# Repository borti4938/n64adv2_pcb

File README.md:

N64 Advanced 2 (PCB)
---

This repository contains all you need files to build your own DIY N64 Advanced board.
Firmware is supplied in another repository.

Please don't ask me for selling a modding.
I either sell some prototypes on some forums marketplaces (which is very unlikely) or I don't have any of the boards.
This is a complete DIY modding project.
Everybody is on his own here.

**WARNING:**
This is an advanced DIY project if you do everything on your own.
You need decent soldering skills.
The FPGA ad Video transmitter have 0.5mm fine pitch with 144pins and 64pins, respectively, and each has an exposed pad below the IC, which has to be soldered to the PCB.
Furthermore, the clocking chip is in a 24-QFN package where the pins are partwise below the IC.
It also has an exposed pad.
Next to it on the board there are some SMD1206 resistor and ferrite bead arrays.

One note on KiCad: please do not use version 7 and stay with version 6.xx.yy, if you want to edit the PCB.
I have to adapt the design files first before there are working as intended in version 7.
Thanks!

## Table of Contents

- [Checklist](https://github.com/borti4938/n64adv2_pcb#checklist-how-to-build-the-project)
- [Assembly](https://github.com/borti4938/n64adv2_pcb#assembly)
- [PCB Specs](https://github.com/borti4938/n64adv2_pcb#pcb-specs)
- [Installation](https://github.com/borti4938/n64adv2_pcb#installation)
  - [1. Open the Console](https://github.com/borti4938/n64adv2_pcb#1-open-the-console)
  - [2. Preparation](https://github.com/borti4938/n64adv2_pcb#2-preparation)
  - [3. Solder Work](https://github.com/borti4938/n64adv2_pcb#3-solder-work)
  - [4. Testing Installtion](https://github.com/borti4938/n64adv2_pcb#4-testing-installation)
  - [5. Put Everything Together](https://github.com/borti4938/n64adv2_pcb#5-put-everything-together)
- [Installation with UltraPIF](https://github.com/borti4938/n64adv2_pcb#installation-with-ultrapif)
- [Jumper Description](https://github.com/borti4938/n64adv2_pcb#jumper-description)

## Checklist: How to build the project

- Use PCB files to order your PCBs. You need the order the main PCB. If you plan to have a clean install, you need to order a flexible PCB, too. You can opt for a fully custom flex-PCB or a partial flex-PCB where you run a FFC cable from flex to main PCB. Important PCB specifications are provided in the [BOM](./doc/n64adv2_BOM.xlsx).
  - Main PCB: either [KiCAD-PCB design file](./pcbs/main/n64adv2.kicad_pcb) or [Gerber files](./gerber/main/)
  - Full Flex PCB: either [KiCAD-PCB design file](./pcbs/flex/rcp2n64adv2.kicad_pcb) or [Gerber files](./gerber/full_flex/)
  - Partial Flex PCB: either [EAGLE-PCB design file](./pcbs/flex/rcp2fpc_v5.brd) or [Gerber files](./gerber/part_flex/)
- If you plan to use solder paste, do not forget to order a stencil for top and bottom, too
- Source the components you need, e.g. from Mouser or Digikey.
  The BOM is available in [here](./doc/n64adv2_BOM.xlsx).
- If you want to use a assembly service (PCBA), you have to generate position files and BOM (in format as the fab requests it) out of the PCB design files. For JLCPCB e.g., there is a [KiCad plugin](https://github.com/Bouni/kicad-jlcpcb-tools) available (which I yet didn't test).
- Wait for everything to arrive
- Assemble your PCB if you haven't use a PCBA service
- Flash the firmware ([firmware releases](https://github.com/borti4938/n64adv2_fw/releases)) after installing:
  - Use the POF programming file named n64adv2\__fpga-device_.pof
  - Using the intelFPGA programmer, JTAG chain is initialized by loading POF file
  - Select CFM0 and UFM for program and verify
  - N64 needs to be powered for flashing
  - Power cycle the N64 after flashing

## PCB Specs

- **Main-PCB** Use PCB files (either [KiCAD-PCB design file](./pcbs/main/n64adv2.kicad_pcb) or [Gerber files](./gerber/main/)) to order your own PCB with following specs (might be not comprehensive)  
  - Size: 89.6mm x 80.0mm
  - Layer: 4
  - FPC thickness: 1.6mm
  - Min hole size: dia 0.3mm / ring 0.6mm or lower
  - Min trace width / spacing: 0.2mm
- **Flex-PCB** Use PCB files (either [KiCAD-PCB design file](./pcbs/flex/rcp2n64adv2.kicad_pcb) or [Gerber files](./gerber/full_flex/)) to order your own PCB with following specs (might be not comprehensive)  
  - Size: 129.6mm x 25.0mm
  - Layer: 2
  - FPC thickness: 0.15mm \[1\]
  - Min hole size: dia 0.25mm / ring 0.45mm or lower
  - Min trace width / spacing: 0.2mm
  - Stiffener: PI top + bottom
  - Stiffener thickness: 0.15mm \[1\]

\[1\] You may have to vary FPC thickness and stiffener thickness depending on the prototype service you are going with. E.g., on my last order I opted for 0.12mm PCB thickness and 0.225mm polyimide thickness.

## Assembly

If you have all components available, you can start assembly your board.
You can use the [interactive BOM](./doc/n64adv2_main_ibom.html), which helps you organizing your work.
It is just a matter of time and effort to assembly everything.

Note that the FPGA has an exposed pad, which needs a good connection.
Otherwise, the FPGA will not boot at all.
Preheat the FPGA with a hot air gun and solder the exposed pad from bottom if you do not use solder paste.
If you only have your solder iron, apply heat from bottom.
You must be patient at this point as there are large GND planes around the FPGA.
You may check the FPGA temperature with your finger on the top side (once it gets too hot to touch, you may stop for soldering for a moment).
Do the same with the other chips which have an exposed pad (U2 and U4).

If you populate X2 with the THT variant, which is the JTAG connector, please short the pins such that they are flush at the bottom side.
Otherwise, the PCB might be lifted in its position which produces unnecessary mechanical stress on PCB and HDMI connector.

Using non-clean flux (rosin based) is obviously recommended.
Even though it is "non-clean" I recommend cleaning everything afterwards (just for the visual finish).

Please double check everything for shorts once you finished your work.
Very important is that the power supply trace do not short to GND.
- 5V against GND (e.g. at input pads)
- 3.3V against GND (e.g. at input pads)
- 2.5V against GND (e.g. at C14)
- 2.5V against GND (e.g. at C15)
- 3.3V against GND (e.g. at C132)
- 1.8V against GND (e.g. at C122)

## Installation

### 1. Open the console

- Remove Jumper Pak / Expansion Pak
- Remove screws from bottom side of the console  
(needs a 4.5mm gamebit tool)
- Lift top housing
- remove inner screws as marked  
(in very last consoles made the heat sink design changed slightly)
- pull out the mainboard
- remove heat sink and RF shield
- **Hint** Now you have the chance to clean up your N64 shell

(image by Zerberus (circuit-board.de user))

### 2. Preparation

It is possible to do a cut or a no-cut installation.
You will need the following parts for it:

1. N64Adv2 PCB
2. Flex Cable
3. Two to four of washers (M3)
4. Thermal pad
  - Cut Mod: appr. 1mm to 1.5mm thickness
  - No Cut Mod: appr. 2.5mm to 3.0mm thickness
5. 3D printed parts:
  - Cut Mod: [USB port round filler](./prints_3d/HalfCut/N64Adv2_USB_RoundFiller.stl), [JTAG spacer](./prints_3d/HalfCut/N64Adv2_JTAG_Spacer.stl) and [MultiOut replacement](./prints_3d/HalfCut/N64Adv2_MultiOut_HalfCut.stl)
  - No Cut Mod: [PCB lift bracket](./prints_3d/NoCut/N64Adv2_PCB_lift.stl) and [MultiOut replacement](./prints_3d/NoCut/N64Adv2_MultiOut_NoCut.stl)

#### 2.1 Shell Preparation Cut Mod

The bottom shell needs a cutout at the MultiOut port.

Mark the place you need to file with either the N64Adv2 PCB or the 3D printed MultiOut replacement.

File down the shell within your markings until the N64Adv2 sits flush on the shell floor.
Consider a tiny space below the HDMI connector.
Cleanup the shell and place the 3D printed parts into the shell.
Make a final fit test as shown.

#### 2.2 Shell Preparation No Cut

There is no need to cut the shell at all with this variant.
All you need is to remove the bottom RF shield from the N64 mainboard.

Place all 3D printed parts and make a fitting test as shown.

### 3. Solder Work

You have the options to either install everything with casual installation wires or using flex cables.
This is just a trade-off between personal installation effort and price.
Personally, I recommend using the flex cable.
Also with the flex cable you have the option to use a fully custom flex or a partial flex which just have a FFC connector on it to run a FFC cable from N64 to N64Adv2.

The instruction shows the installation with the fully custom flex.
The partial flex installation is similar, but not shown here.
The wired installation is not shown and not documented at all! (at least for the moment)

#### 3.1 Prepare the Flex Cable

The flex cable will be routed through the RF shield.
Close to it there are some capacitors.
Gently bend the flex cable between resistors and protection area (stiffener at top and bottom) as shown.
This relaxes routing with as low stress on the flex cable as possible.

If you opt for the partial flex, postpone this step until you have the partial flex installed (after step 3.2).
Measure where the FFC cable needs to be bend.
Apply some insulation tape for cable protection behind the bending area.

#### 3.2 Flex Cable Installation

Place the flex cable to the RCP-NUS output pins 6 to 28 as shown.
Put the solder area on to of the pins.
(However, putting them in front is also possible.)

Secure the cable with some kapton tape or with two solder joints.
Make sure that solder pads and pins are perfectly aligned.
The better the alignment is the easier is the solder work.

Apply solder to all pins.
Double check for shorts and good connections with a continuity tester of a digital multimeter.

Solder 3.3V, 5V, Reset and Controller legs to the N64 as shown.

Short summary:
- Solder the RCP connector side to the RCP-NUS as shown
  - first pin bottom – 6
  - last pin to – 28
- Connect 3.3V to the flex, e.g. taken from C141
- Connect 5V to the flex, e.g. taken from U13
- Connect Ctrl. and reset
  - reset from PIF-NUS pin 27
  - Controller from PIF-NUS pin 16  
  (Make sure that PIF-NUS pin 16 is connected to the middle pin of controller port 1, otherwise search for a suitable connection point)
- If you have a CPLD-based RGB mod, you can use J3 to setup VI-DeBlur on that mod over the N64Adv2
  - J3 has two pads: the left one (directly above the N64Adv2 logo) is the feedback signal, the other one is GND.
    Use a DMM if you are unsure (the GND pad has connection to any GND point on the N64 mainboard if flex is installed)
  - J3 signal pad is high on VI-DeBlur disabled and goes low if enabled

#### 3.2a Flex Cable Version 20231105 (and later)

With Version 20231105 the flex cable was redesigned at the ends to controller and reset connection at the PIF-NUS.

Changes were:
- No components anymore on the thin cable ends for easier handling
- Using a single gate buffer (U1) for the controller line is now mandatory.
- Backup pads for controller and reset connection of the thin cable breaks.
  If cable breaks you can simply cut off the broken cable end and route a separate wire from PIF pin to the backup pad.

#### 4. Testing Installation

At this point it is a good idea to test your installtion.

First you should check for some obvious short at the power rails, e.g. between 3.3V and GND, and between 5V and GND.
If the N64Adv2 board is connected with the flex, you can simply use the input pads on the N64Adv2 board.

Insert a game cartridge, connect HDMI and power, and turn on your N64!
**Important:** If you do not have heatsinks attached to your N64, only test for a brief moment.

Obviously, the firmware of the N64Adv2 must be flashed to the FPGA.

If you see a picture with game output and here some game audio, then everything might be ok.
It's a good idea to run the debug-screen for a quick check.
If something is not ok, the N64Adv2 hardware should boot into the debug screen by default.
Then you have to go for debugging your installation.

Additional information on flashing the firmware and how to debug with the debug screen, can be found the [firmwares repository](https://github.com/borti4938/n64adv2_fw).

#### 5. Put Everything Together

Secure your installation from shorts to the top RF shield with some insulation tape.
There is a risk for shorts where the controller leg of the full flex is routed.
Everything else is safe.

Place some washer (about 0.5mm to 1mm height) at the screw spots left and right of the N64Adv2 flex cable.
From my experience it is easier to secure them with some tape.
Close the RF shield of the N64 then.

Now connect the N64Adv2 PCB to the flex cable.
For the Cut-Mod, also place the bottom RF shield into its place of the N64.
The RF shield does not fit in the no-cut mod variant.

Put the thermal pad on top of the FPGA (U1) of the N64Adv2 board.
This helps with heat dissipation and holds the PCB in its place.

Put everything in the bottom shell.
Do not forget 3D printings.

Secure the N64 with two or three screws and make a small test to see if everything is working.
Do not forget to put in the Jumper Pak or Expansion Pak, otherwise you won't see a picture at all.

If everything works fine, close the whole shell.

## Installation with UltraPIF

This guide assumes that the UltraPIF will be installed after the N64Adv2.
However, other installation orders are possible, too - i.e. UltraPIF first and then N64Adv2 or both alongside.
There are not described, here.
For the ease of debugging, installation one after the other is always recommended.

Also, it is not described, how to open and close the N64.

### 1. Remove PIF-NUS

To remove the PIF-NUS, remove reset and controller connections, first.

The remove the PIF-NUS.

### 2. Install UltraPIF Adapter Board

Put the UltraPIF board into its place.
Connect clock and mode wires and if you want, the RGB led board.
More details on that can be found in the [UltraPIF Repository](https://github.com/jago85/UltraPIF_Hardware/wiki/Installation).

### 3. Connect Flex Cable

Once the UltraPIF Adapter sits in its place, you can reconnect the reset and controller connections of the flex cable.

For the controller connection, you can use the _CON_ pad on the adapter.

For the reset connection you have to go for pin 27 on the adapter.
**DO NOT USE THE _RST_ PAD!** as it acts as an input only.
Fallback functions won't be available if you do so.
Check the connection for shorts to adjacent pins.

### 4. Done

Put the UltraPIF on the UltraPIF Adapter board.

## Jumper Description

**IMPORTANT NOTE**  
Most jumpers are for development reasons and do not need to be touched at all.
This section is only for documentation purposes.

### On main N64Adv2 PCB

##### SJ1 to SJ4 (IO power supply for FPGA Bank 6 and 7)

**Section is outdated. Jumpers had been removed with version 20231119**

Bank B6 and B7 needs 2.5V VCCIO for current implementation.
Since N64Adv2_202200415, these jumpers are closed by default at 2.5V.
Earlier prototypes need a solder joint at 2.5V.
Do not touch 3.3V jumper as current implementation runs IO speed over specifications then.

##### SJ5 (5V power via USB port (X5))

**Section is outdated. Jumper has been removed with version 20231119**

- opened: (default) disable 5V power via USB
- closed: enable 5V power via USB

##### SJ6 (3.3V power via JTAG programmer X4)

**Section is outdated. Jumper has been removed with version 20231119**

- opened: (default) disable 3.3V power via JTAG programmer
- closed: enable 3.3V power via JTAG programmer

#### SJ11 (VI-DeBlur feedback)
- opened: disable feedback for fir flex prototypes
- closed: (default by a trace) feedback enabled

##### SJ31 (SRAM A12)

**Section is outdated. Jumper has been removed with version 20231119**

- opened: (default) use 8Mx16 memory
- closed: use 16Mx16 memory (firmware needs adaptation to work with 16Mx16 memory)

### On flex PCB

##### SJ1

**Section is outdated. Jumpers had been removed with version 20231105**

- opened: use with Schmitt trigger buffer (U1 and C1)
- closed: close jumper if you do not use Schmitt trigger buffer (U1 and C1)

##### J3
- VI-DeBlur feedback for CPLD based RGB mods (see installation section)

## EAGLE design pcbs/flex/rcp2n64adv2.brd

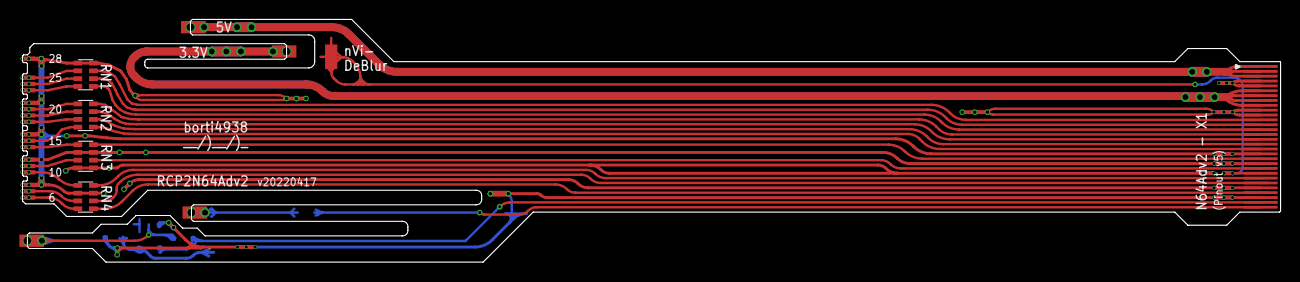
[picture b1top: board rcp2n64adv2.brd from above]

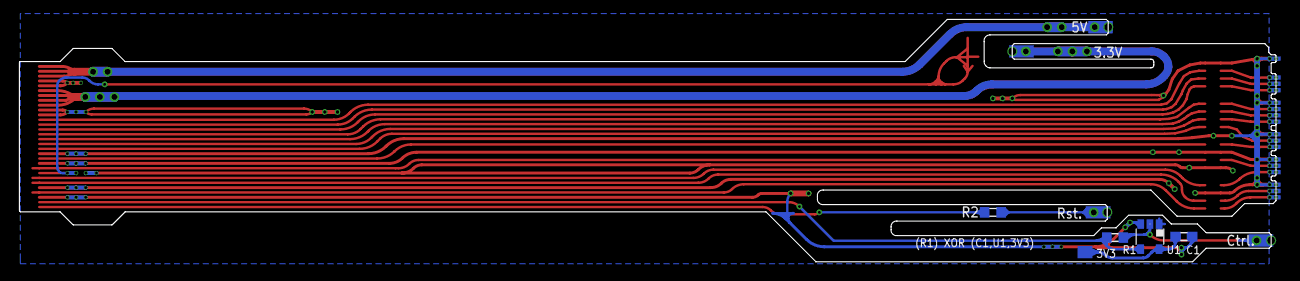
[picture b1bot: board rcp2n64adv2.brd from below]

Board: 2 copper layers, 129.6 x 25.0 mm, 53 parts (26 on the bottom side), 32 nets.

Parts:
+3.3V, +3.3V1, +3.3V2, +5V, +5V1: SMD1,27-2,54
C1: C0603
E$1, E$3, E$4, E$5: CTS742C083
E$2, E$6, E$34, E$35: SMD1,27-2,54
E$7: EDGE-FH12-30S-0.5SH
E$8, E$9, E$10, E$11, E$12, E$13, E$14, E$15, E$16, E$17, E$18, E$19, E$22, E$23, E$24, E$25, E$26, E$27, E$28, E$29, E$30, E$31, E$32, E$33, E$38, E$40, E$41, E$42, E$43, E$44, E$45, E$46, E$47: SMD0,45-1,35
E$20: SMD0.8SQ
GND: SMD0,45-1,35
R1, R2: R0603
U1: DBV_R-PDSO-G5

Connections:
3V3: +3.3V.1, +3.3V1.1, C1.1, E$7.6, E$7.7, E$7.8, E$7.9, E$20.P$1, U1.5
#DSYNC: E$5.1, E$10.P$1, E$31.P$1
#DSYNC.1: E$5.8, E$7.20
+5V: +5V.1, +5V1.1, E$7.1, E$7.2, E$7.3
CTRL: E$6.1, E$35.1, R1.1, U1.2
CTRL.1: E$7.29, R1.2, U1.4
D0: E$3.2, E$19.P$1, E$22.P$1
D0.1: E$3.7, E$7.12
D1: E$3.3, E$18.P$1, E$23.P$1
D1.1: E$3.6, E$7.13
D2: E$3.4, E$17.P$1, E$24.P$1
D2.1: E$3.5, E$7.14
D3: E$4.1, E$15.P$1, E$26.P$1
D3.1: E$4.8, E$7.15
D4: E$4.2, E$14.P$1, E$27.P$1
D4.1: E$4.7, E$7.16
D5: E$4.3, E$13.P$1, E$28.P$1
D5.1: E$4.6, E$7.17
D6: E$4.4, E$11.P$1, E$30.P$1
D6.1: E$4.5, E$7.18
GND: C1.2, E$1.3, E$1.6, E$3.1, E$3.8, E$5.2, E$5.4, E$5.5, E$5.7, E$7.4, E$7.5, E$7.10, E$7.11, E$7.19, E$7.21, E$7.26, E$7.28, E$9.P$1, E$12.P$1, E$16.P$1, E$25.P$1, E$29.P$1, E$32.P$1, E$46.P$1, U1.3
LRCLK: E$1.5, E$38.P$1
LRCLK.1: E$1.4, E$7.24
NVIDEBLUR: +3.3V2.1, E$7.23
RST: E$2.1, E$34.1, R2.1
RST.1: E$7.30, R2.2
SCLK: E$1.8, E$41.P$1
SCLK.1: E$1.1, E$7.27
SDATA: E$1.7, E$40.P$1
SDATA.1: E$1.2, E$7.25
VCLK: E$5.3, E$8.P$1, E$33.P$1
VCLK.1: E$5.6, E$7.22

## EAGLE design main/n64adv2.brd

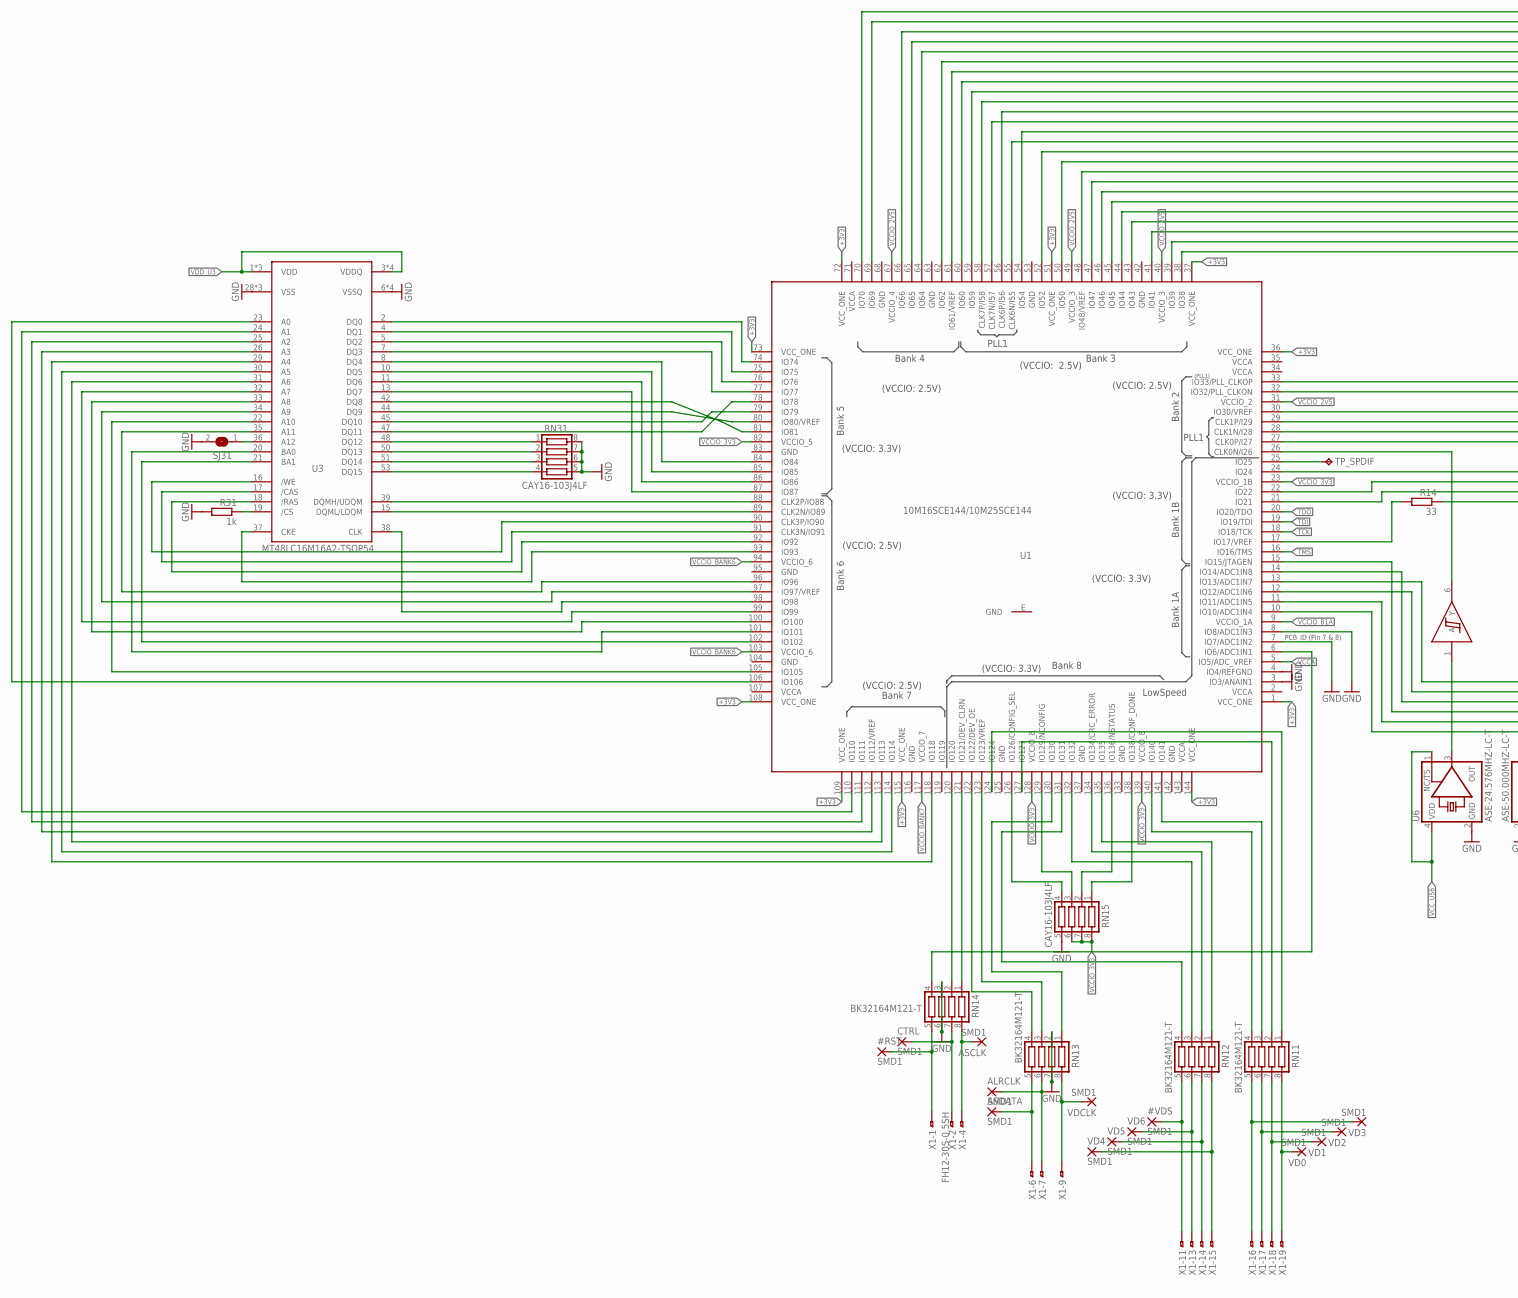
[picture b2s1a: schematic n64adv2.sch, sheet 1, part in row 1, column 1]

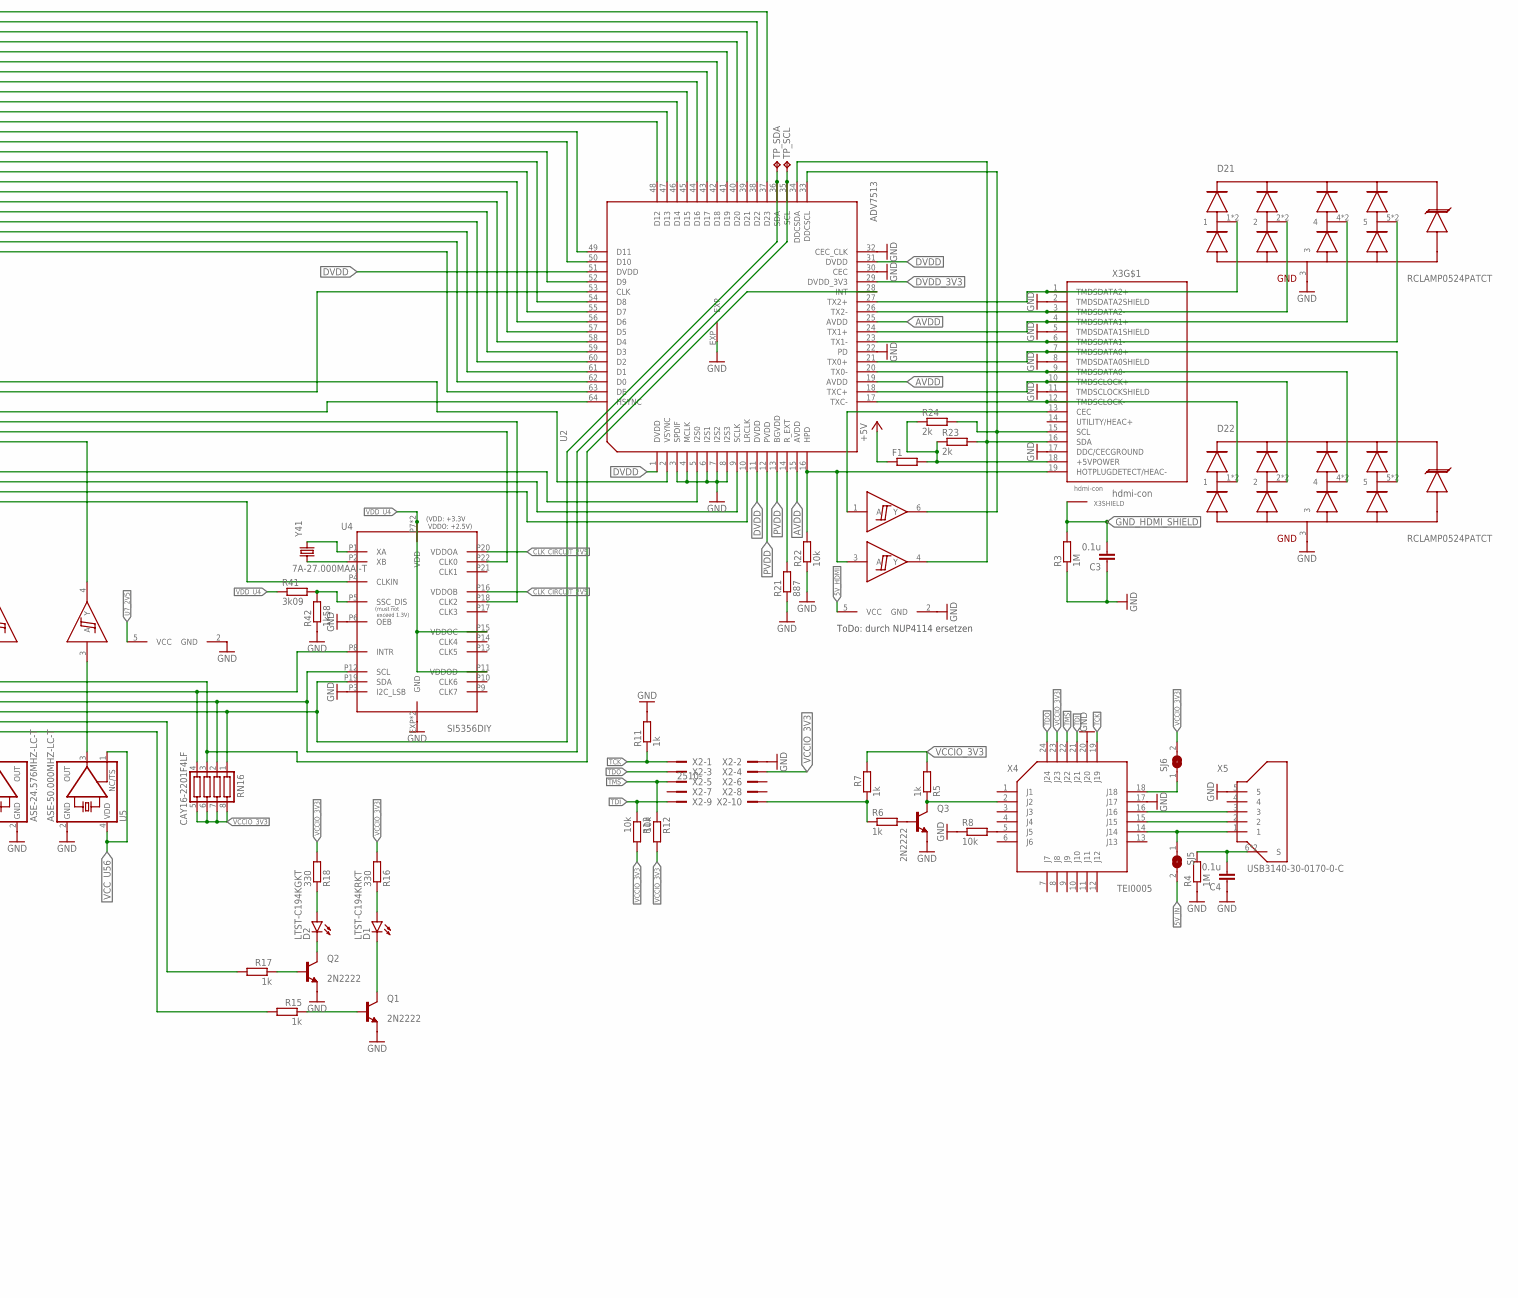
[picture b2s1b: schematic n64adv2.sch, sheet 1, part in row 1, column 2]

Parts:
#RST: SMD1; SMD0,8-1,6
#VDS: SMD1; SMD0,8-1,6
ALRCLK: SMD1; SMD0,8-1,6
ASCLK: SMD1; SMD0,8-1,6
ASDATA: SMD1; SMD0,8-1,6
C3, C4: 0.1u; C0603
CTRL: SMD1; SMD0,8-1,6
D1: LTST-C194KRKT; CHIPLED_0805
D2: LTST-C194KGKT; CHIPLED_0805
D21, D22: RCLAMP0524PATCT; HDMI_RCLAMP
D23: 2G17TI_DBV; SOT-23-6
F1: R-EU_R0603; R0603
Q1, Q2, Q3: 2N2222; SOT23
R3, R4: 1M; R0603
R5, R6, R7, R11, R15, R17, R31: 1k; R0603
R8, R12, R13, R22: 10k; R0603
R14: 33; R0603
R16, R18: 330; R0603
R21: 887; R0603
R23, R24: 2k; R0603
R41: 3k09; R0603
R42: 1k58; R0603
RN11, RN12, RN13, RN14: BK32164M121-T; CTS742C083
RN15, RN31: CAY16-103J4LF; CTS742C083
RN16: CAY16-2201F4LF; CTS742C083
SJ5, SJ6, SJ31: SJSMALL; SJ_SMALL
TP_SCL: TPB1,27; B1,27
TP_SDA: TPB1,27; B1,27
TP_SPDIF: TPB1,27; B1,27
U1: 10M16SCE144/10M25SCE144; EQFP144_2
U2: ADV7513; LQFP64_EP
U3: MT48LC16M16A2-TSOP54; TSOP-54
U4: SI5356DIY; QFN-24-DIY
U5: ASE-50.000MHZ-LC-T; 3.2X2.5_KXO-V96
U6: ASE-24.576MHZ-LC-T; 3.2X2.5_KXO-V96
U7: 2G17TI_DBV; SOT-23-6
VD0, VD1, VD2, VD3, VD4, VD5, VD6: SMD1; SMD0,8-1,6
VDCLK: SMD1; SMD0,8-1,6
X1: FH12-30S-0.5SH
X2: 2510-; PAK100/2500-10
X3: hdmi-con; 685119134923
X4: TEI0005
X5: USB3140-30-0170-0-C; USB-MICRO-VERTICAL-DIY
Y41: 7A-27.000MAAJ-T; 5.0X3.2_2

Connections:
3V3_X5_OUT: SJ6.1, X4.18 (J18)
5V_HDMI: D23.5 (VCC), F1.2, R23.1, R24.1, X3.18 (+5VPOWER)
5V_IN: SJ5.2; also elsewhere on the board
+3V3: U1.1 (VCC_ONE), U1.36 (VCC_ONE), U1.37 (VCC_ONE), U1.51 (VCC_ONE), U1.72 (VCC_ONE), U1.73 (VCC_ONE), U1.108 (VCC_ONE), U1.109 (VCC_ONE), U1.115 (VCC_ONE), U1.144 (VCC_ONE); also elsewhere on the board
+5V: F1.1; also elsewhere on the board
ALRCLK_FPGA_I: RN13.3, U1.123 (IO123/VREF)
ALRCLK_I: ALRCLK.P$1, RN13.6, X1.7
ASCLK_FPGA_I: RN14.1, U1.121 (IO121/DEV_CLRN)
ASCLK_I: ASCLK.P$1, RN14.8, X1.4
ASDATA_FPGA_I: RN13.4, U1.122 (IO122/DEV_OE)
ASDATA_I: ASDATA.P$1, RN13.5, X1.6
AUDIO_MCLK: U6.3 (OUT), U7.1 (A)
AUDIO_MCLK_2V5BUF: U1.26 (CLK0N/I26), U7.6 (Y)
AVDD: U2.15 (AVDD), U2.19 (AVDD), U2.25 (AVDD); also elsewhere on the board
CLK_CIRCUIT_2V5: U4.P16 (VDDOB), U4.P20 (VDDOA); also elsewhere on the board
CLK_TX: U1.32 (IO32/PLL_CLKON), U2.53 (CLK)
CONFIG_SEL: RN15.4, U1.126 (IO126/CONFIG_SEL)
CONF_DONE: RN15.1, U1.138 (IO138/CONF_DONE)
CTRL_FPGA_I: RN14.2, U1.120 (IO120)
CTRL_I: CTRL.P$1, RN14.7, X1.2
DQMH: U1.88 (CLK2P/IO88), U3.39 (DQMH/UDQM)
DQML: U1.89 (CLK2N/IO89), U3.15 (DQML/LDQM)
DVDD: U2.1 (DVDD), U2.11 (DVDD), U2.31 (DVDD), U2.51 (DVDD); also elsewhere on the board
DVDD_3V3: U2.29 (DVDD_3V3); also elsewhere on the board
GND: C3.1, C4.1, D21.3, D22.3, D23.2 (GND), Q1.2 (E), Q2.2 (E), Q3.2 (E), R3.1, R4.1, R8.1, R11.2, R21.1, R22.1, R31.2, R42.1, RN13.2, RN13.7, RN14.3, RN14.6, RN15.5, RN31.5, RN31.6, RN31.7, RN31.8, SJ31.2, U1.3 (IO3/ANAIN1), U1.4 (IO4/REFGND), U1.7 (IO7/ADC1IN2), U1.8 (IO8/ADC1IN3), U1.42 (GND), U1.53 (GND), U1.63 (GND), U1.68 (GND), U1.83 (GND), U1.95 (GND), U1.104 (GND), U1.116 (GND), U1.125 (GND), U1.133 (GND), U1.137 (GND), U1.142 (GND), U1.E (GND), U2.3 (SPDIF), U2.4 (MCLK), U2.6 (I2S1), U2.7 (I2S2), U2.8 (I2S3), U2.22 (PD), U2.30 (CEC), U2.32 (CEC_CLK), U2.EXP, U3.6 (VSSQ), U3.12 (VSSQ), U3.28 (VSS), U3.41 (VSS), U3.46 (VSSQ), U3.52 (VSSQ), U3.54 (VSS), U4.EXP (GND), U4.P3 (I2C_LSB), U4.P6 (OEB), U4.P23 (GND), U5.2 (GND), U6.2 (GND), U7.2 (GND), X2.2, X3.2 (TMDSDATA2SHIELD), X3.5 (TMDSDATA1SHIELD), X3.8 (TMDSDATA0SHIELD), X3.11 (TMDSCLOCKSHIELD), X3.17 (DDC/CECGROUND), X4.17 (J17), X4.20 (J20), X5.5; also elsewhere on the board
GND_HDMI_SHIELD: C3.2, R3.2, X3.SHELL (SHIELD), X3.SHELL1 (SHIELD), X3.SHELL2 (SHIELD), X3.SHELL3 (SHIELD)
HDMI_CEC: D23.1 (A), X3.13 (CEC)
HDMI_CLK_MAIN_I: U1.28 (CLK1N/I28), U4.P22 (CLK0)
HDMI_CLK_SUB_I: U1.29 (CLK1P/I29), U4.P18 (CLK2)
HDMI_HPD: D23.3 (A), R22.2, U2.16 (HPD), X3.19 (HOTPLUGDETECT/HEAC-)
HDMI_SCL: D23.6 (Y), R24.2, U2.33 (DDCSCL), X3.15 (SCL)
HDMI_SDA: D23.4 (Y), R23.2, U2.34 (DDCSDA), X3.16 (SDA)
HDMI_TX0+: D22.5, D22.6 (5), U2.21 (TX0+), X3.7 (TMDSDATA0+)
HDMI_TX0-: D22.4, D22.7 (4), U2.20 (TX0-), X3.9 (TMDSDATA0-)
HDMI_TX1+: D21.4, D21.7 (4), U2.24 (TX1+), X3.4 (TMDSDATA1+)
HDMI_TX1-: D21.5, D21.6 (5), U2.23 (TX1-), X3.6 (TMDSDATA1-)
HDMI_TX2+: D21.1, D21.10 (1), U2.27 (TX2+), X3.1 (TMDSDATA2+)
HDMI_TX2-: D21.2, D21.9 (2), U2.26 (TX2-), X3.3 (TMDSDATA2-)
HDMI_TXC+: D22.2, D22.9 (2), U2.18 (TXC+), X3.10 (TMDSCLOCK+)
HDMI_TXC-: D22.1, D22.10 (1), U2.17 (TXC-), X3.12 (TMDSCLOCK-)
I2S0: U1.24 (IO24), U2.5 (I2S0)
INT_ADV7513: RN16.3, U1.13 (IO13/ADC1IN7), U2.28 (INT)
INT_SI5356: RN16.4, U1.12 (IO12/ADC1IN6), U4.P8 (INTR)
LED1: Q1.1 (B), R15.1
LED1_FPGA: R15.2, U1.10 (IO10/ADC1IN4)
LED2: Q2.1 (B), R17.1
LED2_FPGA: R17.2, U1.11 (IO11/ADC1IN5)
LRCLK: U1.21 (IO21), U2.10 (LRCLK)
unnamed: D1.A, R16.1
unnamed: D2.C, Q2.3 (C)
unnamed: D1.C, Q1.3 (C)
unnamed: R41.2, R42.2, U4.P5 (SSC_DIS)
unnamed: U4.P1 (XA), Y41.2
unnamed: U4.P2 (XB), Y41.1
unnamed: R6.1, R7.1, X2.10
unnamed: Q3.1 (B), R6.2
unnamed: R21.2, U2.14 (R_EXT)
unnamed: D2.A, R18.1
NCONFIG: RN15.3, U1.129 (IO129/NCONFIG)
NRST_FPGA_IO: RN14.4, U1.6 (IO6/ADC1IN1)
NRST_IO: #RST.P$1, RN14.5, X1.1
NSTATUS: RN15.2, U1.136 (IO136/NSTATUS)
NVDS_FPGA_I: RN12.4, U1.131 (IO131)
NVDS_I: #VDS.P$1, RN12.5, X1.11
PVDD: U2.12 (PVDD), U2.13 (BGVDD); also elsewhere on the board
SCL: RN16.2, TP_SCL.TP, U1.14 (IO14/ADC1IN8), U2.35 (SCL), U4.P12 (SCL)
SCLK: U1.22 (IO22), U2.9 (SCLK)
SDA: RN16.1, TP_SDA.TP, U1.15 (IO15/JTAGEN), U2.36 (SDA), U4.P19 (SDA)
SDRAM_A0: U1.106 (IO106), U3.23 (A0)
SDRAM_A1: U1.110 (IO110), U3.24 (A1)
SDRAM_A2: U1.111 (IO111), U3.25 (A2)
SDRAM_A3: U1.112 (IO112/VREF), U3.26 (A3)
SDRAM_A4: U1.118 (IO118), U3.29 (A4)
SDRAM_A5: U1.114 (IO114), U3.30 (A5)
SDRAM_A6: U1.113 (IO113), U3.31 (A6)
SDRAM_A7: U1.99 (IO99), U3.32 (A7)
SDRAM_A8: U1.100 (IO100), U3.33 (A8)
SDRAM_A9: U1.97 (IO97/VREF), U3.34 (A9)
SDRAM_A10: U1.105 (IO105), U3.22 (A10)
SDRAM_A11: U1.96 (IO96), U3.35 (A11)
SDRAM_A12: SJ31.1, U3.36 (A12)
SDRAM_BA0: U1.102 (IO102), U3.21 (BA1)
SDRAM_BA1: U1.101 (IO101), U3.20 (BA0)
SDRAM_CKE: U1.93 (IO93), U3.37 (CKE)
SDRAM_CLK: U1.98 (IO98), U3.38 (CLK)
SDRAM_DQ0: U1.74 (IO74), U3.2 (DQ0)
SDRAM_DQ1: U1.75 (IO75), U3.4 (DQ1)
SDRAM_DQ2: U1.76 (IO76), U3.5 (DQ2)
SDRAM_DQ3: U1.77 (IO77), U3.7 (DQ3)
SDRAM_DQ4: U1.84 (IO84), U3.8 (DQ4)
SDRAM_DQ5: U1.85 (IO85), U3.10 (DQ5)
SDRAM_DQ6: U1.86 (IO86), U3.11 (DQ6)
SDRAM_DQ7: U1.87 (IO87), U3.13 (DQ7)
SDRAM_DQ8: U1.81 (IO81), U3.42 (DQ8)
SDRAM_DQ9: U1.80 (IO80/VREF), U3.44 (DQ9)
SDRAM_DQ10: U1.79 (IO79), U3.45 (DQ10)
SDRAM_DQ11: U1.78 (IO78), U3.47 (DQ11)
SDRAM_DQ12: RN31.1, U3.48 (DQ12)
SDRAM_DQ13: RN31.2, U3.50 (DQ13)
SDRAM_DQ14: RN31.3, U3.51 (DQ14)
SDRAM_DQ15: RN31.4, U3.53 (DQ15)
SDRAM_NCAS: U1.91 (CLK3N/IO91), U3.17 (/CAS)
SDRAM_NCS: R31.1, U3.19 (/CS)
SDRAM_NRAS: U1.92 (IO92), U3.18 (/RAS)
SDRAM_NWE: U1.90 (CLK3P/IO90), U3.16 (/WE)
SPDIF: TP_SPDIF.TP, U1.25 (IO25)
SYS_CLK: U5.3 (OUT), U7.3 (A)
SYS_CLK_2V5_BUF: U1.27 (CLK0P/I27), U7.4 (Y)
TCK: R11.1, U1.18 (IO18/TCK), X2.1, X4.19 (J19)
TDI: R13.1, U1.19 (IO19/TDI), X2.9, X4.21 (J21)
TDO: U1.20 (IO20/TDO), X2.3, X4.24 (J24)
TMS: R12.1, U1.16 (IO16/TMS), X2.5, X4.22 (J22)
TX_B0: U1.39 (IO39), U2.62 (D0)
TX_B1: U1.41 (IO41), U2.61 (D1)
TX_B2: U1.43 (IO43), U2.60 (D2)
TX_B3: U1.44 (IO44), U2.59 (D3)
TX_B4: U1.45 (IO45), U2.58 (D4)
TX_B5: U1.46 (IO46), U2.57 (D5)
TX_B6: U1.47 (IO47), U2.56 (D6)
TX_B7: U1.48 (IO48/VREF), U2.55 (D7)
TX_DE: U1.38 (IO38), U2.63 (DE)
TX_G0: U1.50 (IO50), U2.54 (D8)
TX_G1: U1.52 (IO52), U2.52 (D9)
TX_G2: U1.55 (CLK6N/I55), U2.50 (D10)
TX_G3: U1.54 (IO54), U2.49 (D11)
TX_G4: U1.57 (CLK7N/I57), U2.48 (D12)
TX_G5: U1.56 (CLK6P/I56), U2.47 (D13)
TX_G6: U1.58 (CLK7P/I58), U2.46 (D14)
TX_G7: U1.59 (IO59), U2.45 (D15)
TX_HSYNC: U1.30 (IO30/VREF), U2.64 (HSYNC)
TX_R0: U1.60 (IO60), U2.44 (D16)
TX_R1: U1.61 (IO61/VREF), U2.43 (D17)
TX_R2: U1.62 (IO62), U2.42 (D18)
TX_R3: U1.64 (IO64), U2.41 (D19)
TX_R4: U1.65 (IO65), U2.40 (D20)
TX_R5: U1.66 (IO66), U2.39 (D21)
TX_R6: U1.69 (IO69), U2.38 (D22)
TX_R7: U1.70 (IO70), U2.37 (D23)
TX_VSYNC: U1.33 (IO33/PLL_CLKOP), U2.2 (VSYNC)
U7_2V5: U7.5 (VCC); also elsewhere on the board
USB_D+: X4.16 (J16), X5.3
USB_D-: X4.15 (J15), X5.2
USB_GND_SHIELD: C4.2, R4.2, X5.6 (S), X5.7 (S)
USB_VBUS: SJ5.1, X4.14 (J14), X5.1
VCCA: U1.2 (VCCA), U1.5 (IO5/ADC_VREF), U1.34 (VCCA), U1.35 (VCCA), U1.71 (VCCA), U1.107 (VCCA), U1.143 (VCCA); also elsewhere on the board
VCCIO_2V5: U1.31 (VCCIO_2), U1.40 (VCCIO_3), U1.49 (VCCIO_3), U1.67 (VCCIO_4); also elsewhere on the board
VCCIO_3V3: R5.2, R7.2, R12.2, R13.2, R16.2, R18.2, RN15.6, RN15.7, RN15.8, RN16.5, RN16.6, RN16.7, RN16.8, SJ6.2, U1.23 (VCCIO_1B), U1.82 (VCCIO_5), U1.128 (VCCIO_8), U1.139 (VCCIO_8), X2.4, X4.23 (J23); also elsewhere on the board
VCCIO_B1A: U1.9 (VCCIO_1A); also elsewhere on the board
VCCIO_BANK6: U1.94 (VCCIO_6), U1.103 (VCCIO_6); also elsewhere on the board
VCCIO_BANK7: U1.117 (VCCIO_7); also elsewhere on the board
VCC_U56: U5.1 (TS), U5.4 (VDD), U6.1 (TS), U6.4 (VDD); also elsewhere on the board
VCLK_FEEDBACK: R14.2, U1.17 (IO17/VREF)
VCLK_FEEDBACK_BUF: R14.1, U4.P4 (CLKIN)
VD0_FPGA_I: RN11.1, U1.124 (IO124)
VD0_I: RN11.8, VD0.P$1, X1.19
VD1_FPGA_I: RN11.2, U1.127 (IO127)
VD1_I: RN11.7, VD1.P$1, X1.18
VD2_FPGA_I: RN11.3, U1.141 (IO141)
VD2_I: RN11.6, VD2.P$1, X1.17
VD3_FPGA_I: RN11.4, U1.140 (IO140)
VD3_I: RN11.5, VD3.P$1, X1.16
VD4_FPGA_I: RN12.1, U1.135 (IO135)
VD4_I: RN12.8, VD4.P$1, X1.15
VD5_FPGA_I: RN12.2, U1.134 (IO134/CRC_ERROR)
VD5_I: RN12.7, VD5.P$1, X1.14
VD6_FPGA_I: RN12.3, U1.132 (IO132)
VD6_I: RN12.6, VD6.P$1, X1.13
VDCLK_FPGA_I: RN13.1, U1.130 (IO130)
VDCLK_I: RN13.8, VDCLK.P$1, X1.9
VDD_U3: U3.1 (VDD), U3.3 (VDDQ), U3.9 (VDDQ), U3.14 (VDD), U3.27 (VDD), U3.43 (VDDQ), U3.49 (VDDQ); also elsewhere on the board
VDD_U4: R41.1, U4.P7 (VDD), U4.P11 (VDDOD), U4.P15 (VDDOC), U4.P24 (VDD); also elsewhere on the board
X4_OEN: Q3.3 (C), R5.1, X4.2 (J2)
X5_UART_RX: R8.2, X4.5 (J5)

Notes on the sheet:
(VCCIO: 3.3V)
(VCCIO: 2.5V)
(VCCIO: 2.5V)
(must not exceed 1.3V)
(VDD: +3.3V VDDO: +2.5V)
PCB_ID (Pin 7 & 8)
ToDo: durch NUP4114 ersetzen

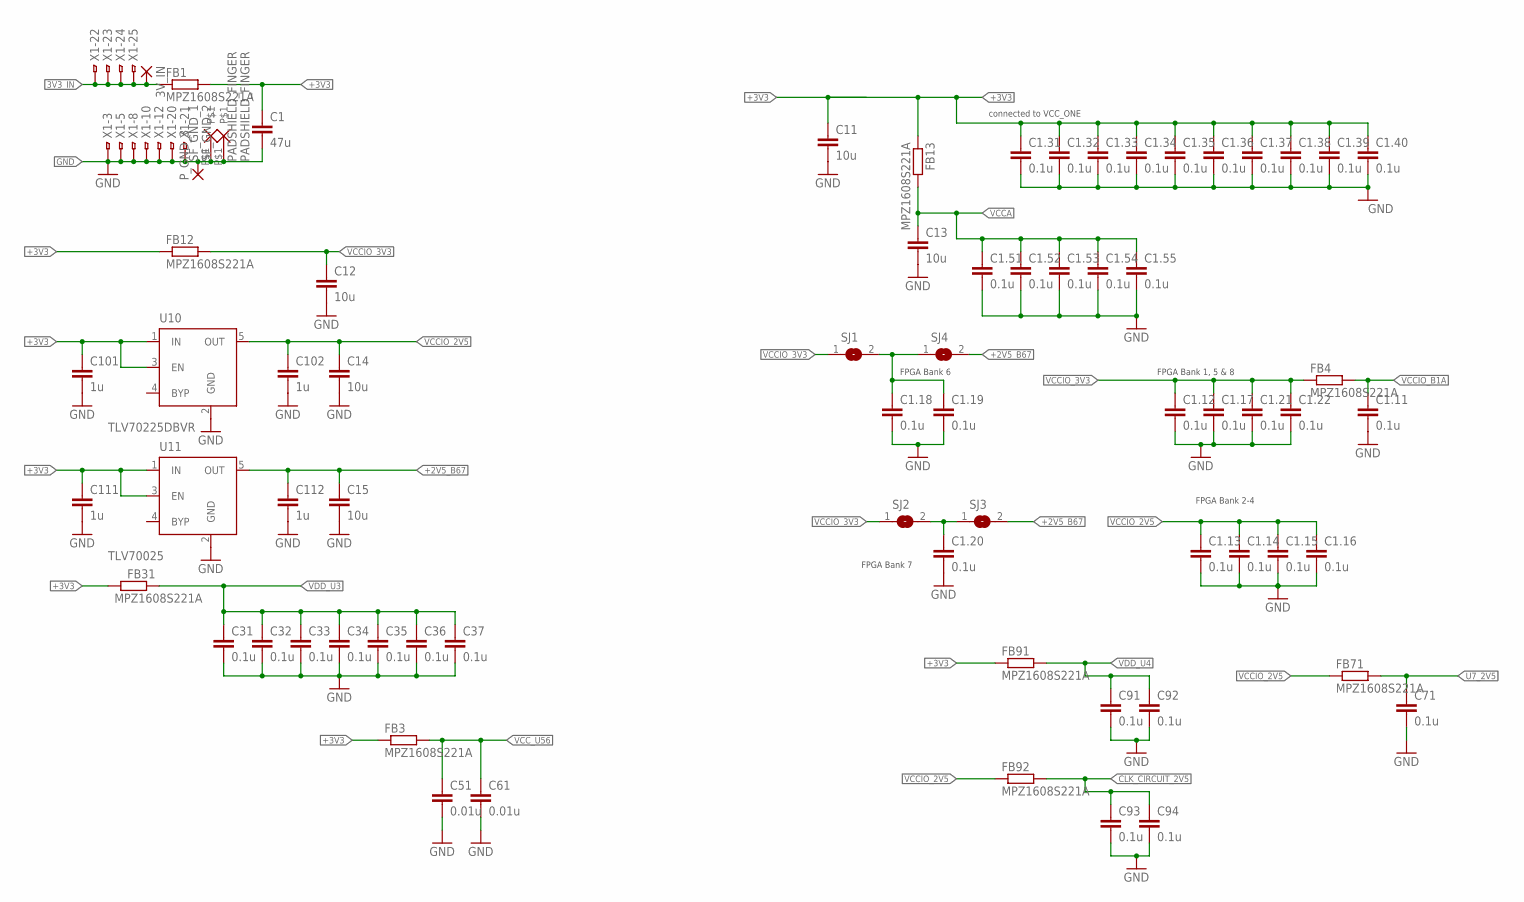
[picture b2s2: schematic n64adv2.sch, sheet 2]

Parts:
3V_IN: SMD2; SMD1,27-2,54
C1: 47u; C0805
C1.11, C1.12, C1.13, C1.14, C1.15, C1.16, C1.17, C1.18, C1.19, C1.20, C1.21, C1.22, C1.31, C1.32, C1.33, C1.34, C1.35, C1.36, C1.37, C1.38, C1.39, C1.40, C1.51, C1.52, C1.53, C1.54, C1.55, C31, C32, C33, C34, C35, C36, C37, C71, C91, C92, C93, C94: 0.1u; C0603
C11, C12, C13, C14, C15: 10u; C0805
C51, C61: 0.01u; C0603
C101, C102, C111, C112: 1u; C0603
FB1, FB3, FB4, FB12, FB13, FB31, FB71, FB91, FB92: MPZ1608S221A; R0603
P_GND_3: SMD2; SMD1,27-2,54
SF_GND_1, SF_GND_2: PADSHIELD_FINGER; GND_FINGER_PAD
SJ1, SJ2, SJ3, SJ4: SJSMALL; SJ_SMALL
U10: TLV70225DBVR; SOT23-5
U11: TLV70025; SOT23-5
X1: FH12-30S-0.5SH

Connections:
3V3_IN: 3V_IN.1, FB1.1, X1.22, X1.23, X1.24, X1.25
+2V5_B67: C15.1, C112.1, SJ3.2, SJ4.2, U11.5 (OUT)
+3V3: C1.1, C1.31.1, C1.32.1, C1.33.1, C1.34.1, C1.35.1, C1.36.1, C1.37.1, C1.38.1, C1.39.1, C1.40.1, C11.1, C101.1, C111.1, FB1.2, FB3.1, FB12.1, FB13.1, FB31.1, FB91.1, U10.1 (IN), U10.3 (EN), U11.1 (IN), U11.3 (EN); also elsewhere on the board
CLK_CIRCUIT_2V5: C93.1, C94.1, FB92.2; also elsewhere on the board
GND: C1.2, C1.11.2, C1.12.2, C1.13.2, C1.14.2, C1.15.2, C1.16.2, C1.17.2, C1.18.2, C1.19.2, C1.20.2, C1.21.2, C1.22.2, C1.31.2, C1.32.2, C1.33.2, C1.34.2, C1.35.2, C1.36.2, C1.37.2, C1.38.2, C1.39.2, C1.40.2, C1.51.2, C1.52.2, C1.53.2, C1.54.2, C1.55.2, C11.2, C12.2, C13.2, C14.2, C15.2, C31.2, C32.2, C33.2, C34.2, C35.2, C36.2, C37.2, C51.2, C61.2, C71.2, C91.2, C92.2, C93.2, C94.2, C101.2, C102.2, C111.2, C112.2, P_GND_3.1, SF_GND_1.P$1, SF_GND_2.P$1, U10.2 (GND), U11.2 (GND), X1.3, X1.5, X1.8, X1.10, X1.12, X1.20, X1.21; also elsewhere on the board
U7_2V5: C71.1, FB71.2; also elsewhere on the board
VCCA: C1.51.1, C1.52.1, C1.53.1, C1.54.1, C1.55.1, C13.1, FB13.2; also elsewhere on the board
VCCIO_2V5: C1.13.1, C1.14.1, C1.15.1, C1.16.1, C14.1, C102.1, FB71.1, FB92.1, U10.5 (OUT); also elsewhere on the board
VCCIO_3V3: C1.12.1, C1.17.1, C1.21.1, C1.22.1, C12.1, FB4.1, FB12.2, SJ1.1, SJ2.1; also elsewhere on the board
VCCIO_B1A: C1.11.1, FB4.2; also elsewhere on the board
VCCIO_BANK6: C1.18.1, C1.19.1, SJ1.2, SJ4.1; also elsewhere on the board
VCCIO_BANK7: C1.20.1, SJ2.2, SJ3.1; also elsewhere on the board
VCC_U56: C51.1, C61.1, FB3.2; also elsewhere on the board
VDD_U3: C31.1, C32.1, C33.1, C34.1, C35.1, C36.1, C37.1, FB31.2; also elsewhere on the board
VDD_U4: C91.1, C92.1, FB91.2; also elsewhere on the board

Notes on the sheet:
FPGA Bank 6
FPGA Bank 7
FPGA Bank 1, 5 & 8
FPGA Bank 2-4
connected to VCC_ONE

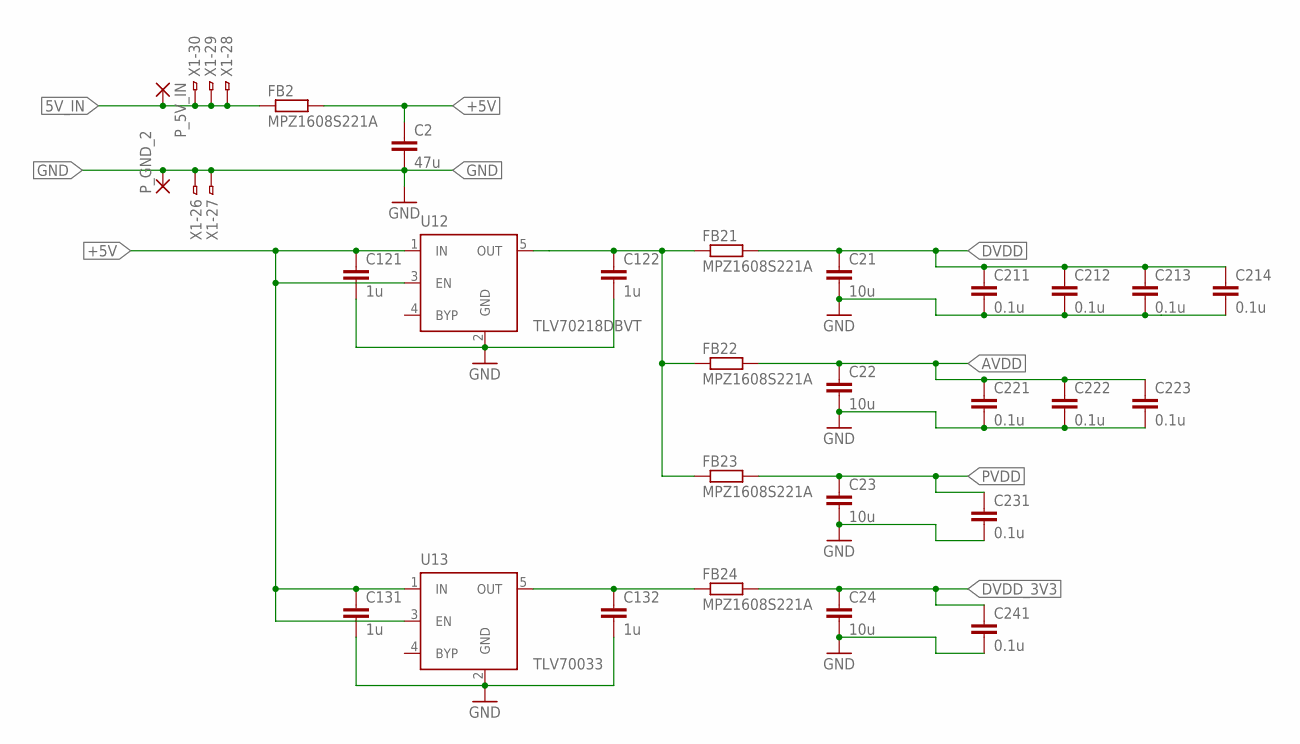
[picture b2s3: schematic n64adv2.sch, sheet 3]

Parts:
C2: 47u; C0805
C21, C22, C23, C24: 10u; C0805
C121, C122, C131, C132: 1u; C0603
C211, C212, C213, C214, C221, C222, C223, C231, C241: 0.1u; C0603
FB2, FB21, FB22, FB23, FB24: MPZ1608S221A; R0603
P_5V_IN: SMD2; SMD1,27-2,54
P_GND_2: SMD2; SMD1,27-2,54
U12: TLV70218DBVT; SOT23-5
U13: TLV70033; SOT23-5
X1: FH12-30S-0.5SH

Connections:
1.8V_PRE: C122.1, FB21.1, FB22.1, FB23.1, U12.5 (OUT)
3.3V_PRE: C132.1, FB24.1, U13.5 (OUT)
5V_IN: FB2.1, P_5V_IN.1, X1.28, X1.29, X1.30; also elsewhere on the board
+5V: C2.1, C121.1, C131.1, FB2.2, U12.1 (IN), U12.3 (EN), U13.1 (IN), U13.3 (EN); also elsewhere on the board
AVDD: C22.1, C221.1, C222.1, C223.1, FB22.2; also elsewhere on the board
DVDD: C21.1, C211.1, C212.1, C213.1, C214.1, FB21.2; also elsewhere on the board
DVDD_3V3: C24.1, C241.1, FB24.2; also elsewhere on the board
GND: C2.2, C21.2, C22.2, C23.2, C24.2, C121.2, C122.2, C131.2, C132.2, C211.2, C212.2, C213.2, C214.2, C221.2, C222.2, C223.2, C231.2, C241.2, P_GND_2.1, U12.2 (GND), U13.2 (GND), X1.26, X1.27; also elsewhere on the board
PVDD: C23.1, C231.1, FB23.2; also elsewhere on the board

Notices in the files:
main/lite/n64adv2.brd:
PCB (c) 2018 by Peter Bartmann aka borti4938
main/n64adv2.brd:
PCB (c) 2021 by Peter Bartmann aka borti4938
parts and their libraries:
crystal-geyer_V1_0: Copyright: Geyer-Electronic
WE_IO_rev18a: Copyright: Würth Elektronik
